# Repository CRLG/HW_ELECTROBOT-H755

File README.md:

# HW_ELECTROBOT-H755
Carte électronique ELECTROBOT H755 (double coeur)

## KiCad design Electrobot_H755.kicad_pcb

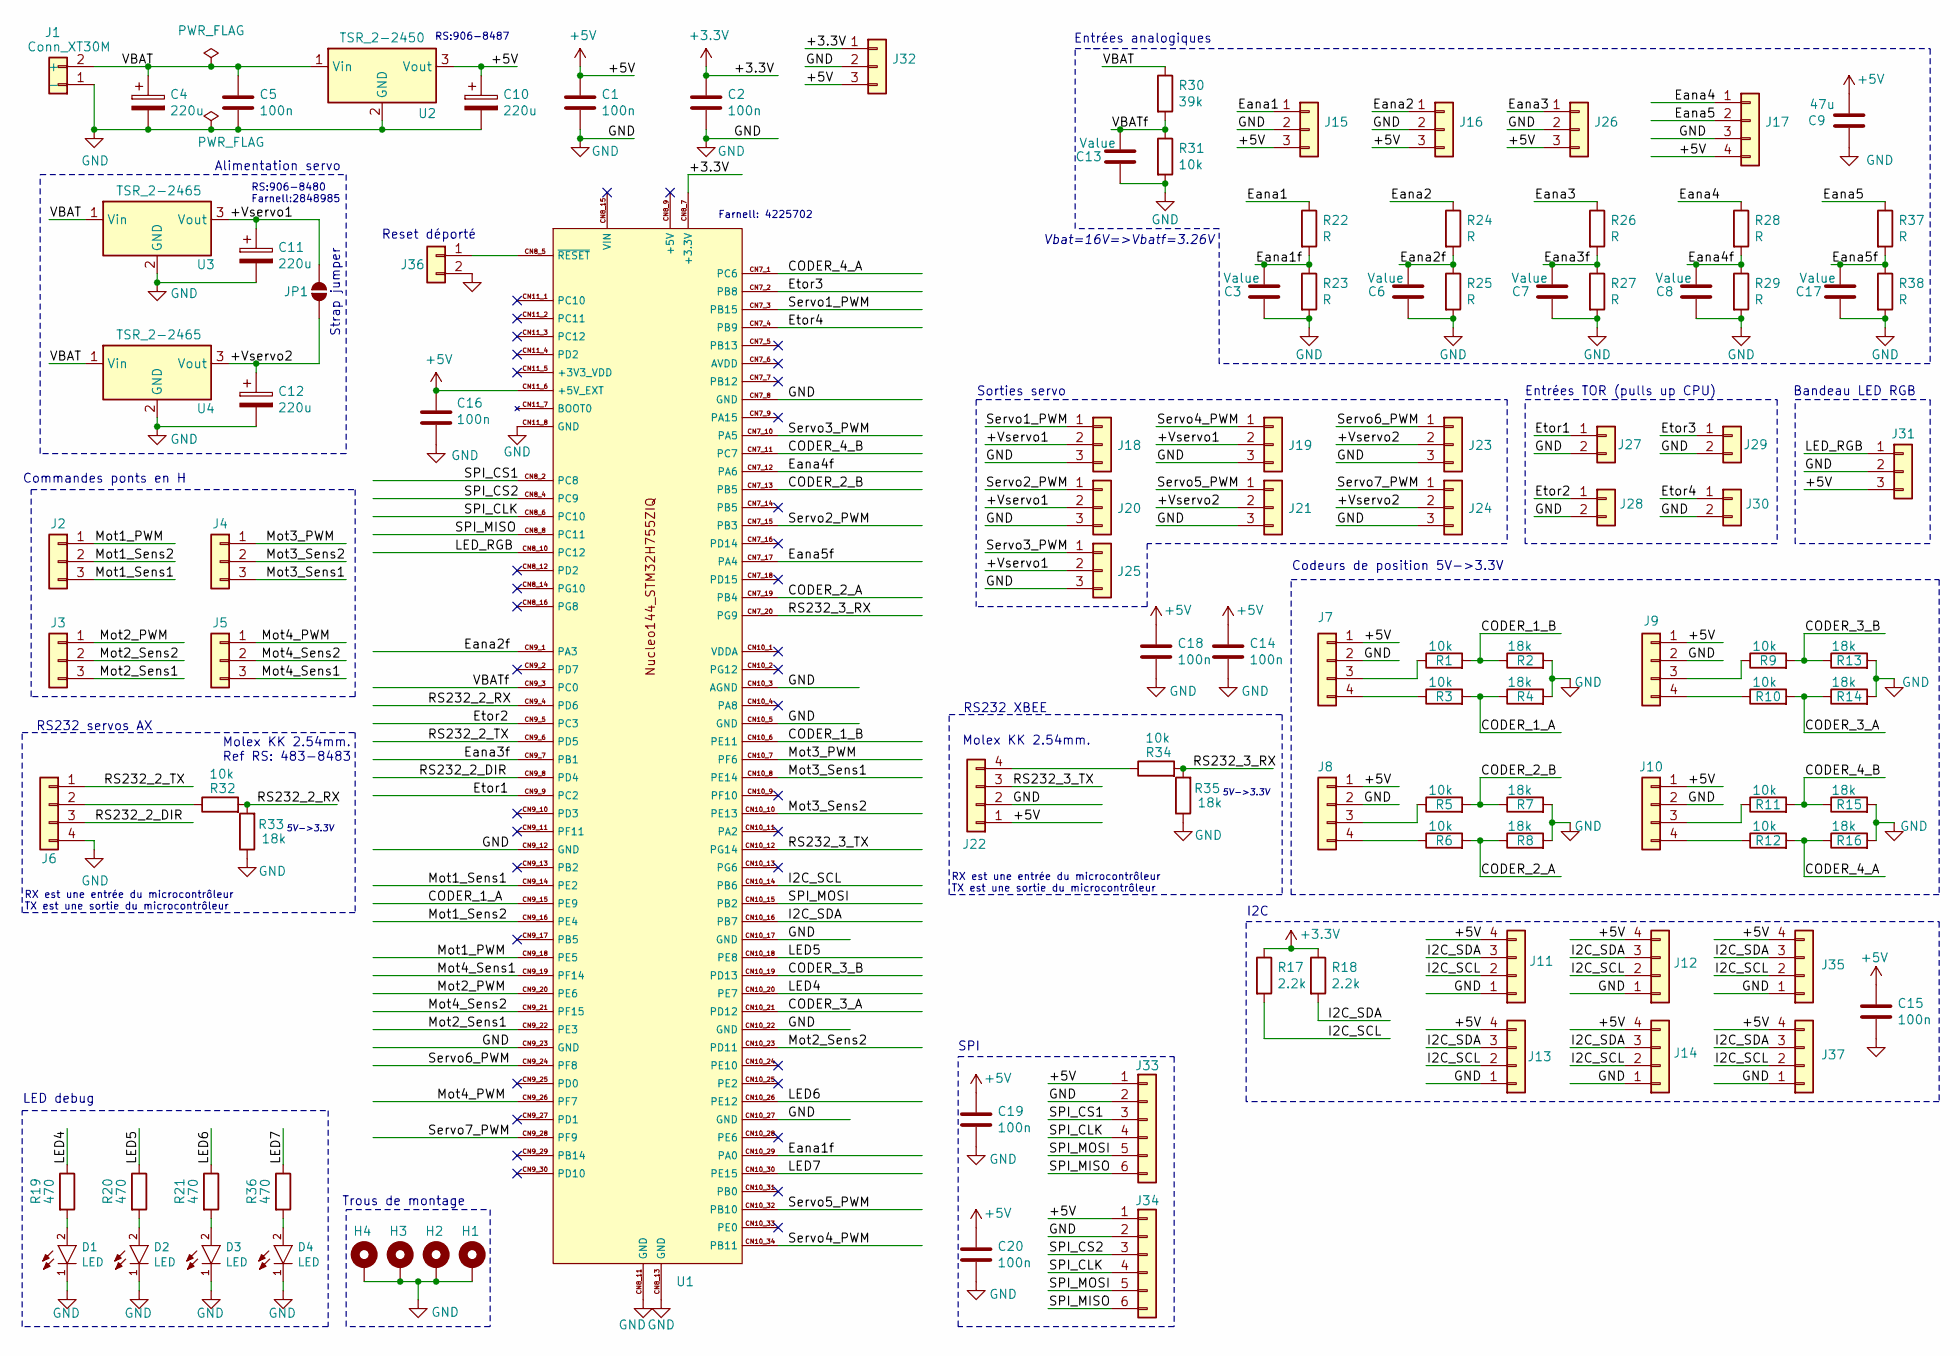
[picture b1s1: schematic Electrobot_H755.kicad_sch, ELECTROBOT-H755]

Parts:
C1, C2, C5, C14, C15, C16, C18, C19, C20: 100n; C_1206_3216Metric
C3, C6, C7, C8, C13, C17: Value; C_1206_3216Metric
C4, C10, C11, C12: 220u; C_Radial_D8.0mm_H11.5mm_P3.50mm
C9: 47u; C_1206_3216Metric
D1, D2, D3, D4: LED; LED_1206_3216Metric
H1, H2, H3, H4: MountingHole_Pad; MountingHole_3.2mm_M3_Pad
J1: Conn_XT30M; AMASS_XT30UPB-M_1x02_P5.0mm_Vertical
J2, J3, J4, J5: Conn_01x04; Molex_KK-254_AE-6410-03A_1x03_P2.54mm_Vertical
J6, J7, J8, J9, J10, J11, J12, J13, J14, J17, J22, J35, J37: Conn_01x04; Molex_KK-254_AE-6410-04A_1x04_P2.54mm_Vertical
J15, J16, J26, J31, J32: Conn_01x03; Molex_KK-254_AE-6410-03A_1x03_P2.54mm_Vertical
J18, J19, J20, J21, J23, J24, J25: Conn_01x03; Servomotor-3x254
J27, J28, J29, J30, J36: Conn_01x02; Molex_KK-254_AE-6410-02A_1x02_P2.54mm_Vertical
J33, J34: Conn_01x06; Molex_KK-254_AE-6410-06A_1x06_P2.54mm_Vertical
JP1: SolderJumper_2_Open; PinHeader_1x02_P2.54mm_Vertical
R1, R3, R5, R6, R9, R10, R11, R12, R31, R32, R34: 10k; R_1206_3216Metric
R2, R4, R7, R8, R13, R14, R15, R16, R33, R35: 18k; R_1206_3216Metric
R17, R18: 2.2k; R_1206_3216Metric
R19, R20, R21, R36: 470; R_1206_3216Metric
R22, R23, R24, R25, R26, R27, R28, R29, R37, R38: R; R_1206_3216Metric
R30: 39k; R_1206_3216Metric
U1: ST_Zio_EXT5V_Connectors_Nucleo144_ExtensionShield
U2: TSR_2-2450; Converter_DCDC_TRACO_TSR-1_THT
U3, U4: TSR_2-2465; Converter_DCDC_TRACO_TSR-1_THT

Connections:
+3.3V: C2.1, J32.1, R17.1, R18.1, U1.CN8_7 (+3.3V)
+5V: C1.1, C9.2, C10.1, C14.1, C15.1, C16.1, C18.1, C19.1, C20.1, J7.1, J8.1, J9.1, J10.1, J11.4, J12.4, J13.4, J14.4, J15.3, J16.3, J17.4, J22.1, J26.3, J31.3, J32.3, J33.1, J34.1, J35.4, J37.4, U1.CN11_6 (+5V_EXT), U2.3 (Vout)
/+Vservo1: C11.1, J18.2, J19.2, J20.2, J25.2, JP1.2 (B), U3.3 (Vout)
/+Vservo2: C12.1, J21.2, J23.2, J24.2, JP1.1 (A), U4.3 (Vout)
/CODER_1_A: R3.2, R4.1, U1.CN9_15 (PE9)
/CODER_1_B: R1.2, R2.1, U1.CN10_6 (PE11)
/CODER_2_A: R6.2, R8.1, U1.CN7_19 (PB4)
/CODER_2_B: R5.2, R7.1, U1.CN7_13 (PB5)
/CODER_3_A: R10.2, R14.1, U1.CN10_21 (PD12)
/CODER_3_B: R9.2, R13.1, U1.CN10_19 (PD13)
/CODER_4_A: R12.2, R16.1, U1.CN7_1 (PC6)
/CODER_4_B: R11.2, R15.1, U1.CN7_11 (PC7)
/Eana1: J15.1, R22.1
/Eana1f: C3.2, R22.2, R23.1, U1.CN10_29 (PA0)
/Eana2: J16.1, R24.1
/Eana2f: C6.2, R24.2, R25.1, U1.CN9_1 (PA3)
/Eana3: J26.1, R26.1
/Eana3f: C7.2, R26.2, R27.1, U1.CN9_7 (PB1)
/Eana4: J17.1, R28.1
/Eana4f: C8.2, R28.2, R29.1, U1.CN7_12 (PA6)
/Eana5: J17.2, R37.1
/Eana5f: C17.2, R37.2, R38.1, U1.CN7_17 (PA4)
/Etor1: J27.1, U1.CN9_9 (PC2)
/Etor2: J28.1, U1.CN9_5 (PC3)
/Etor3: J29.1, U1.CN7_2 (PB8)
/Etor4: J30.1, U1.CN7_4 (PB9)
/I2C_SCL: J11.2, J12.2, J13.2, J14.2, J35.2, J37.2, R17.2, U1.CN10_14 (PB6)
/I2C_SDA: J11.3, J12.3, J13.3, J14.3, J35.3, J37.3, R18.2, U1.CN10_16 (PB7)
/LED4: R19.1, U1.CN10_20 (PE7)
/LED5: R20.1, U1.CN10_18 (PE8)
/LED6: R21.1, U1.CN10_26 (PE12)
/LED7: R36.1, U1.CN10_30 (PE15)
/LED_RGB: J31.1, U1.CN8_10 (PC12)
/Mot1_PWM: J2.1, U1.CN9_18 (PE5)
/Mot1_Sens1: J2.3, U1.CN9_14 (PE2)
/Mot1_Sens2: J2.2, U1.CN9_16 (PE4)
/Mot2_PWM: J3.1, U1.CN9_20 (PE6)
/Mot2_Sens1: J3.3, U1.CN9_22 (PE3)
/Mot2_Sens2: J3.2, U1.CN10_23 (PD11)
/Mot3_PWM: J4.1, U1.CN10_7 (PF6)
/Mot3_Sens1: J4.3, U1.CN10_8 (PE14)
/Mot3_Sens2: J4.2, U1.CN10_10 (PE13)
/Mot4_PWM: J5.1, U1.CN9_26 (PF7)
/Mot4_Sens1: J5.3, U1.CN9_19 (PF14)
/Mot4_Sens2: J5.2, U1.CN9_21 (PF15)
/RS232_2_DIR: J6.3, U1.CN9_8 (PD4)
/RS232_2_RX: R32.2, R33.2, U1.CN9_4 (PD6)
/RS232_2_TX: J6.1, U1.CN9_6 (PD5)
/RS232_3_RX: R34.2, R35.2, U1.CN7_20 (PG9)
/RS232_3_TX: J22.3, U1.CN10_12 (PG14)
/SPI_CLK: J33.4, J34.4, U1.CN8_6 (PC10)
/SPI_CS1: J33.3, U1.CN8_2 (PC8)
/SPI_CS2: J34.3, U1.CN8_4 (PC9)
/SPI_MISO: J33.6, J34.6, U1.CN8_8 (PC11)
/SPI_MOSI: J33.5, J34.5, U1.CN10_15 (PB2)
/Servo1_PWM: J18.1, U1.CN7_3 (PB15)
/Servo2_PWM: J20.1, U1.CN7_15 (PB3)
/Servo3_PWM: J25.1, U1.CN7_10 (PA5)
/Servo4_PWM: J19.1, U1.CN10_34 (PB11)
/Servo5_PWM: J21.1, U1.CN10_32 (PB10)
/Servo6_PWM: J23.1, U1.CN9_24 (PF8)
/Servo7_PWM: J24.1, U1.CN9_28 (PF9)
/VBAT: C4.1, C5.1, J1.2 (+), R30.1, U2.1 (Vin), U3.1 (Vin), U4.1 (Vin)
/VBATf: C13.2, R30.2, R31.1, U1.CN9_3 (PC0)
GND: C1.2, C2.2, C3.1, C4.2, C5.2, C6.1, C7.1, C8.1, C9.1, C10.2, C11.2, C12.2, C13.1, C14.2, C15.2, C16.2, C17.1, C18.2, C19.2, C20.2, D1.1 (C), D2.1 (C), D3.1 (C), D4.1 (C), H1.1, H2.1, H3.1, H4.1, J1.1 (-), J6.4, J7.2, J8.2, J9.2, J10.2, J11.1, J12.1, J13.1, J14.1, J15.2, J16.2, J17.3, J18.3, J19.3, J20.3, J21.3, J22.2, J23.3, J24.3, J25.3, J26.2, J27.2, J28.2, J29.2, J30.2, J31.2, J32.2, J33.2, J34.2, J35.1, J36.2, J37.1, R2.2, R4.2, R7.2, R8.2, R13.2, R14.2, R15.2, R16.2, R23.2, R25.2, R27.2, R29.2, R31.2, R33.1, R35.1, R38.2, U1.CN7_8 (GND), U1.CN8_11 (GND), U1.CN8_13 (GND), U1.CN9_12 (GND), U1.CN9_23 (GND), U1.CN10_3 (AGND), U1.CN10_5 (GND), U1.CN10_17 (GND), U1.CN10_22 (GND), U1.CN10_27 (GND), U1.CN11_8 (GND), U2.2 (GND), U3.2 (GND), U4.2 (GND)
unnamed: D1.2 (A), R19.2
unnamed: D2.2 (A), R20.2
unnamed: D3.2 (A), R21.2
unnamed: D4.2 (A), R36.2
unnamed: J6.2, R32.1
unnamed: J7.3, R1.1
unnamed: J7.4, R3.1
unnamed: J8.3, R5.1
unnamed: J8.4, R6.1
unnamed: J9.3, R9.1
unnamed: J9.4, R10.1
unnamed: J10.3, R11.1
unnamed: J10.4, R12.1
unnamed: J22.4, R34.1
unnamed: J36.1, U1.CN8_5 (~RESET)

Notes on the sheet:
Sorties servo
RX est une entrée du microcontrôleur TX est une sortie du microcontrôleur
5V->3.3V
Vbat=16V=>Vbatf=3.26V
Alimentation servo
Codeurs de position 5V->3.3V
Commandes ponts en H
Trous de montage
RS232 XBEE
Molex KK 2.54mm. Ref RS: 483-8483
Entrées TOR (pulls up CPU)
Farnell: 4225702
RS:906-8487
RS:906-8480 Farnell:2848985
LED debug
SPI
RS232 servos AX
Molex KK 2.54mm.
I2C
Bandeau LED RGB
Entrées analogiques
Reset déporté
Strap jumper

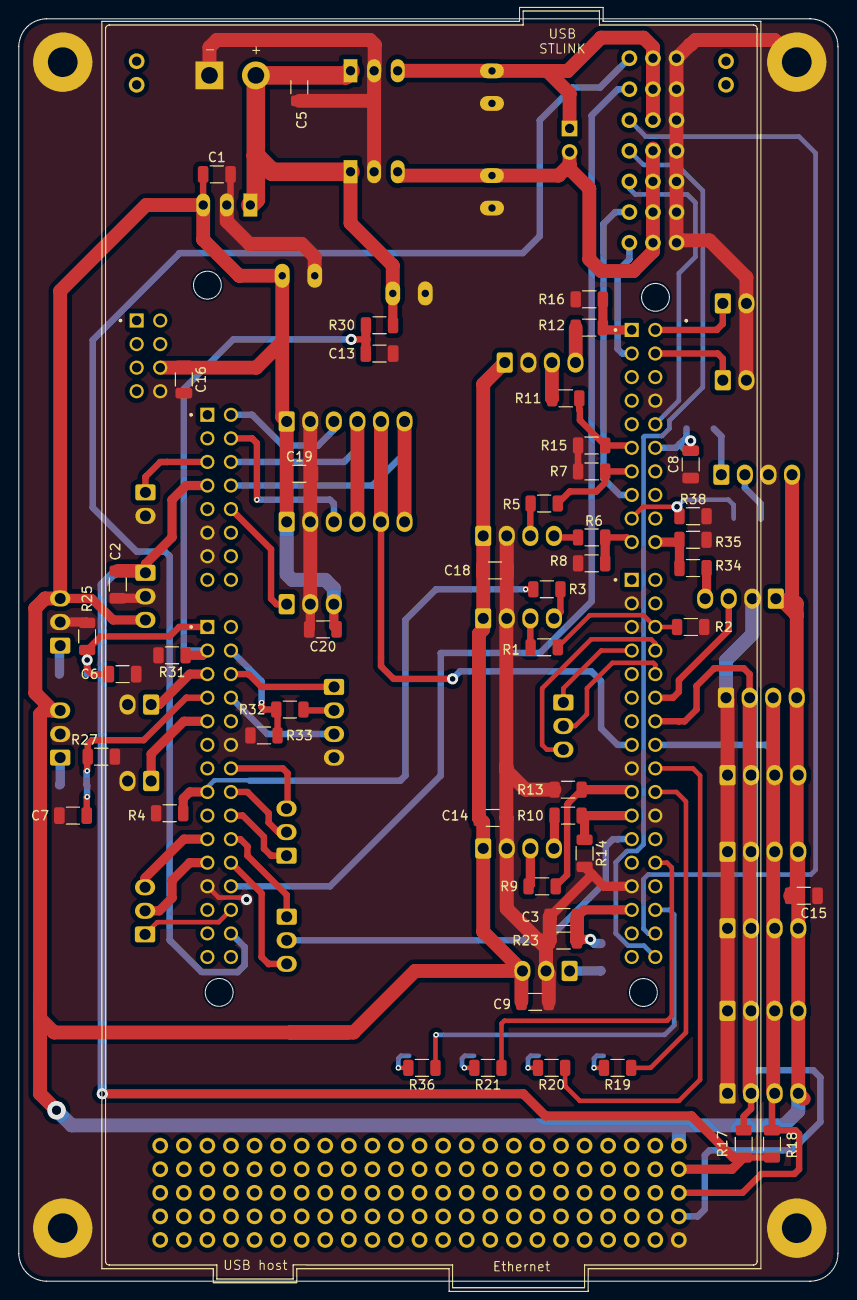
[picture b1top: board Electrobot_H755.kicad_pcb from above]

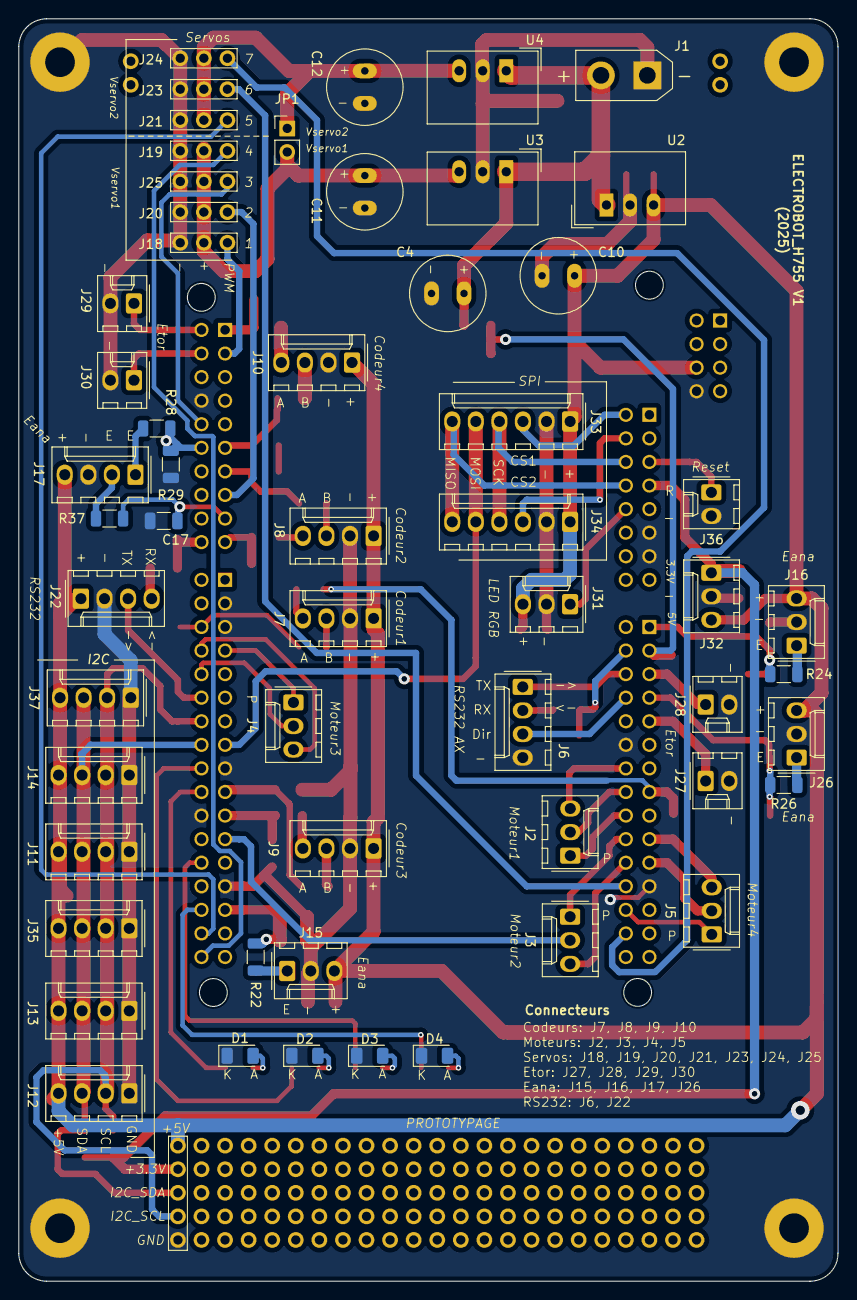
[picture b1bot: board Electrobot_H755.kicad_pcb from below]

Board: 2 copper layers, 88.3 x 136.0 mm, 108 parts (56 on the bottom side), 80 nets.

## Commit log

2024-12-17 Mise en place de l'ossature : ajout du sous-module KICAD_LIB
2024-12-21 Version initiale du projet (en cours)
2024-12-21 Ajout du fichier .gitignore
2024-12-21 Mise à jour du sous-module KICAD_LIB
2025-01-05 Mise à jour du schéma
2025-01-05 Suppression des libs qui n'existent plus dans la table des symbols utilisés
2025-01-11 Evolutions/corrections suite à la séance de relecture du 08/01/2025 avec Ben et LaGuiche
    - Correction entrée analogique Eana1
    - Ajout d'un connecteur de reset déporté
    - Ajout d'un 5ème connecteur I2C
    - Changement de l'empreinte du jumper Vservo1 - 2
2025-01-12 Correction empreinte condensateur
2025-01-13 Inversion Eana5f et Eana3f pour faciliter le routage
2025-01-13 Ajout des références commerciales RS et Farnell pour certains composants
2025-01-26 Routage de la carte + fichiers gerber
2025-01-26 Export schéma en .pdf
2025-01-26 Bords de la carte arrondis + ajout sérigraphie manquante
2025-01-26 Ajout sérigraphie manquante
2025-01-26 Mise à jour sérigraphie manquante
2025-01-26 Sérigraphie complétée
2025-01-26 Sérigraphie complétér
2025-03-24 Ajout de la BOM .html (généré par le plugin Kicad)
2025-03-30 Correction des valeurs de résistances pour les UART servos AX et XBEE
2025-03-30 Ajout des références pour les supports sécables femelle 2.54
2025-04-23 Ajout des références et valeurs manquantes sur le schéma
